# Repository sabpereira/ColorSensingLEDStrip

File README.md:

# Color Sensing LED Strip

This repository conatins the documentation and relevant files for the Color Sensing LED Strip controller, a controller that allows for the user to scan a desired color to set an LED strip to the color, as well as allowing other methods of user input. 

## Overview
The Color Sensing LED Strip controller enables the user to set the color of an LED strip by choosing to scan a light source of a desired color to replicate (such as from a phone), select the desired RGB values, or choose from a preset selection of colors, including the last color scanned. Please review the video below or [click here]( https://youtu.be/J2j3cKCgywg) for a demo of the controller in action.

The user interface displays text and menus OLED ".96 display, with selections made through the use of a rotary encoder. The color spectrometer Adafruit AS7341 is used to scan the desired color. Adafruit DotStars are used for the LEDs.

## User Interface 

The Color Sensing LED Strip experiments with various methods of user input with only a rotary encoder and a button as input. The original concept for the user interface can be viewed and interacted with in `User Experience.pptx`. The actual implemented UI is a simplified version of the original concept. The PCB layout was also designed with the user experience in mind, as will be explained in the relevant section.

## Hardware

The relevant Kicad files and bill of materials can be found in the `hardware/` folder of this repository.

### Schematic 

The folowing schematic each of the components used in the controller and how they connect. The Arduino Nano communicates with the color spectrometer and LCD screen via I2C. 

### PCB Layout

The PCB layout was planned out for user convenience. The power supply is connected on the left, with the LEDs connected on the right for ease of setup wherever the LEDs are intented to be placed. The LCD screen and rotary encoder are placed towards the bottom of the board for easy access by the user, while the color spectrometer is placed high on the board such that the LCD screen is still visible while the scan is taking place.

## Software 

Source code can be found in the `src/` folder of this repository.

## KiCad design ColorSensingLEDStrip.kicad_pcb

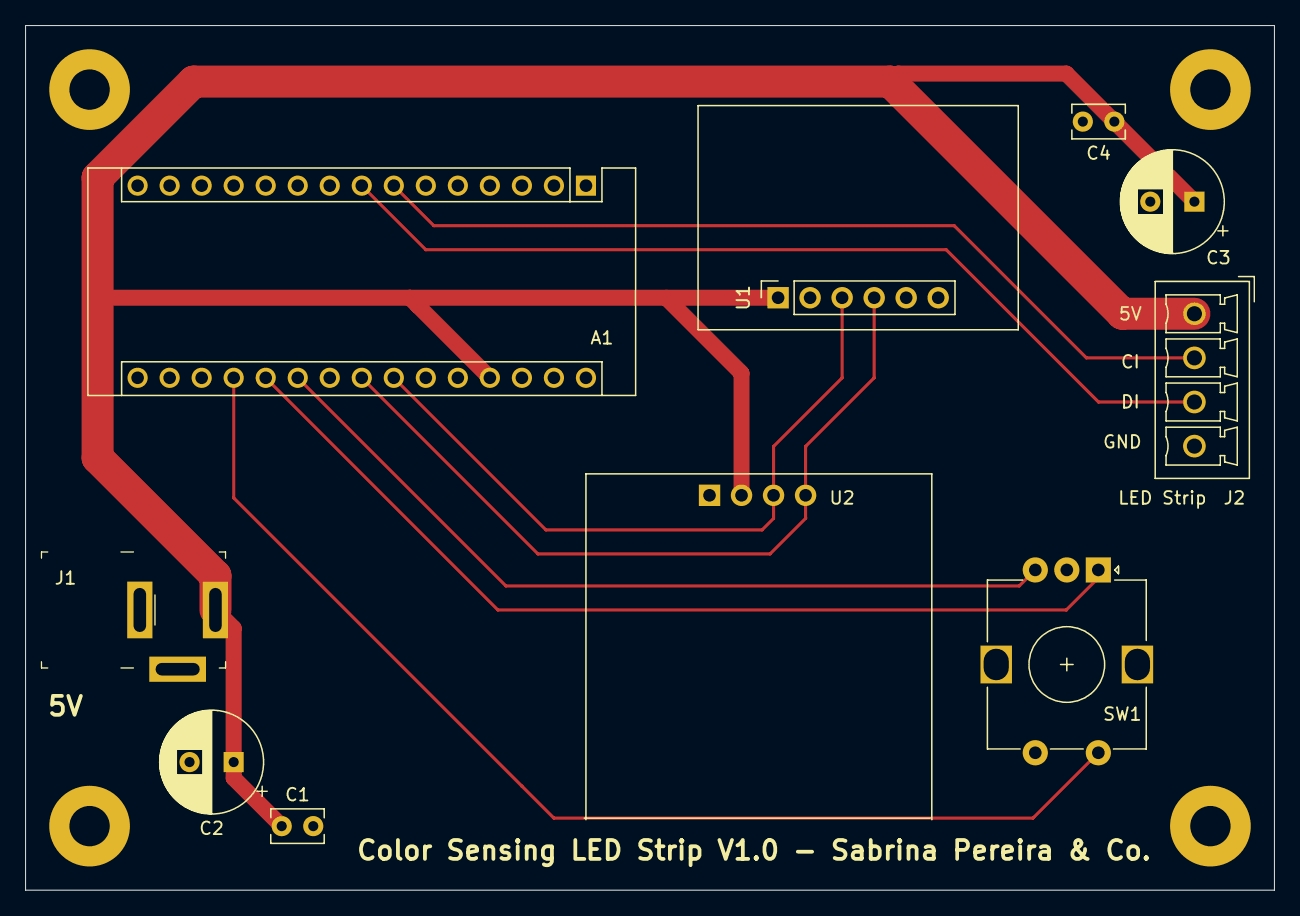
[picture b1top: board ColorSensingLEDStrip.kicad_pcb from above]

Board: 2 copper layers, 99.1 x 68.6 mm, 10 parts (0 on the bottom side), 9 nets.

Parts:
A1: Arduino_Nano_v3.x; Arduino_Nano
C1, C4: 0.1 uf; C_Rect_L4.0mm_W2.5mm_P2.50mm
C2: 100 uf; CP_Radial_D8.0mm_P3.50mm
C3: 1000 uf; CP_Radial_D8.0mm_P3.50mm
J1: Barrel_Jack_Switch; Barrel_Jack_5.5mmODx2.1mmID_PJ-202A
J2: 4-Wire Screw Terminal; PhoenixContact_MCV_1,5_4-G-3.5_1x04_P3.50mm_Vertical
SW1: Rotary_Encoder_Switch; RotaryEncoder_Alps_EC12E-Switch_Vertical_H20mm
U1: Adafruit_AS7341; Adafruit_AS7341_PinSocket
U2: OLED; OLED_0.96

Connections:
+5V: A1.27, C1.1, C2.1, C3.1, C4.1, J1.1, J2.1, U1.1, U2.2
ENCODER_A: A1.20, SW1.A
ENCODER_B: A1.21, SW1.B
ENCODER_SW: A1.19, SW1.S1
GND: A1.4, A1.29, C1.2, C2.2, C3.2, C4.2, J1.2, J2.4, SW1.C, SW1.S2, U1.2, U2.1
I2C_SCL: A1.24, U1.3, U2.3
I2C_SDA: A1.23, U1.4, U2.4
LED_CI: A1.7, J2.2
LED_DI: A1.8, J2.3

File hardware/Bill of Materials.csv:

Qty,Value,Vendor,Price
1,Arduino_Nano_v3.x,Amazon,13.99
1,Barrel_Jack_Switch,DK: CP-202A-ND,0.6
1,4-Wire Screw Terminal,DK: 277-5744-ND,2.58
2,10k,DK: CF18JT10K0,0.1
1,Rotary_Encoder_Switch,Amazon,7.99
1,Adafruit_AS7341,"Adafruit: 4698, DK: 1528-4698-ND",15.95
1,OLED,Amazon,11.99
1,LED_Strip_1m,Adafruit: 2239,29.95
2,0.1 uf,DK: BC1084TR-ND,0.23
1,100 uf,DK: 493-10478-1-ND,0.49
1,1000 uf,DK: 1189-4233-1-ND,0.52
1,JST SM 4 Wire connectors,Adafruit: 578,1.5
1,Barrel Power Supply,Amazon,12.99
1,6-Pin Socket,DK: PPPC061LFBN-RC,0.53

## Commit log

2020-11-24 Initial commit of project files
2020-11-29 v2.0 PCB files
2020-12-19 Folder cleaning
